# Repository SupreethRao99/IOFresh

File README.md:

# IOFresh
Team Members:
[Aviral Agarwal](https://github.com/Avr8),
[Supreeth Rao](https://github.com/SupreethRao99),
[Akshat Gupta](https://github.com/akshat302),
[Shubham Singh](https://github.com/ishusingh99),
[Rumit Kumar Sharma](https://github.com/rumit7)

# Product Summary:

IOFresh is an IOT based Air Freshener. It comprises a basic Air Freshener which is integrated with an Air Quality monitoring module. This Air Quality module provides us with a standard Air Quality Index and also with the composition of the surrounding air (mainly Carbon Monoxide(CO), Methane(CH4) and LPG) 
This device will be user controlled using a user friendly mobile application developed in accordance with this specific device. The mobile application will provide us with features like Periodic Air Quality Monitoring, ALERTS regarding the Air Quality in its surroundings

# User Persona:
## Persona 1: Working Professional
In today’s day and age we observe that a house is empty for upwards of 10 hours a day and any LPG leakage or toxic gases produced due to fires will not be attended to immediately. IOFresh’s suite of sensors will report the ongoings in their house in real-time allowing them to take necessary action like alerting emergency services.

## Persona 2: Families   
IOFresh would be a great addition to people and families that like to entertain. The Air Freshener aspect of IOFresh provides a way to set the atmosphere for a gathering or a party by infusing the air with pleasant aromas. 

# Simulation 
You can try our arduino simulation on tinkercad. The link to our simulation can be found [here](https://www.tinkercad.com/things/bUrlJmCXl2o)

# Contents Of the Repository:
   1) Board Schematic Made using Autodesk Eagle
   2) 3D modelled Images of IOFRESH made Using Fusion 360
   3) IO-FRESH arduino code used for simulation in tinkercad
   4) Specification/Features

# Directory Structure
```
IOFresh
├── 3D\ Renders
│   ├── 3D\ Model\ Of\ IO-Fresh
│   ├── IOFresh-Product-mockup\ v2.png
│   ├── IOFresh-Product-mockup_2021-cprofile.png
│   ├── IOFresh-Product-mockup_2021-left-profile.png
│   └── IOFresh-components-1.png
├── Board\ Layout\ and\ Schematic
│   ├── Schematic.pdf
│   ├── eagle.epf
│   ├── iofresh-board-layout.pdf
│   ├── iofresh.b#1
│   ├── iofresh.b#2
│   ├── iofresh.b#3
│   ├── iofresh.brd
│   ├── iofresh.pro
│   ├── iofresh.s#1
│   ├── iofresh.s#2
│   ├── iofresh.s#3
│   ├── iofresh.s#4
│   └── iofresh.sch
├── IO\ FRESH\ Specifications_Features.pdf
├── IOFresh-Arduino\ Simulation.ino
├── LICENSE
└── README.md
```
# Licensing 
IOFresh is licensed under the [MIT License](https://github.com/SupreethRao99/IOFresh/blob/main/LICENSE)

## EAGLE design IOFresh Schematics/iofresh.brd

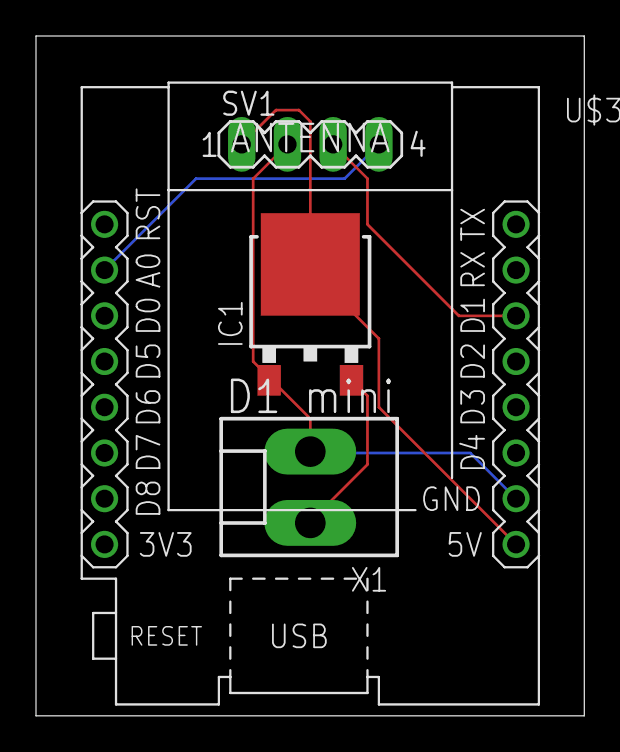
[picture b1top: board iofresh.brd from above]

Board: 2 copper layers, 30.5 x 37.8 mm, 4 parts (0 on the bottom side), 5 nets.

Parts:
IC1: LM1117DT-5.0; TO252
SV1: MA04-1
U$3: WEMOS-D1-MINI
X1: KK-156-2

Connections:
unnamed: IC1.2, X1.1
unnamed: IC1.3, SV1.1, U$3.JP2.8
unnamed: IC1.1, SV1.2, U$3.JP2.7, X1.2
unnamed: SV1.3, U$3.JP2.3
unnamed: SV1.4, U$3.JP1.2

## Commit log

2021-06-27 Add schematic files
    Autodesk Eagle schematic files of IOFresh have been added. Eagle ECAD software is required to view these files
2021-06-27 Add updated schematic
2021-08-04 Added Schematic in PDF
2021-09-09 Added Arduino simulation code
2021-09-10 Create 3D Model Of IO-Fresh
2021-09-10 Add files via upload
    The PCB Board Layout Of the main Circuitry Made using Eagle
2021-09-10 Refactored repository
2021-10-03 Update IOFresh-Arduino Simulation.ino
    Cleaned the simulation code and made changes in the comments

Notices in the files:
parts and their libraries:
diy-modules: Released under the Creative Commons Attribution 4.0 International License: http://creativecommons.org/licenses/by/4.0
